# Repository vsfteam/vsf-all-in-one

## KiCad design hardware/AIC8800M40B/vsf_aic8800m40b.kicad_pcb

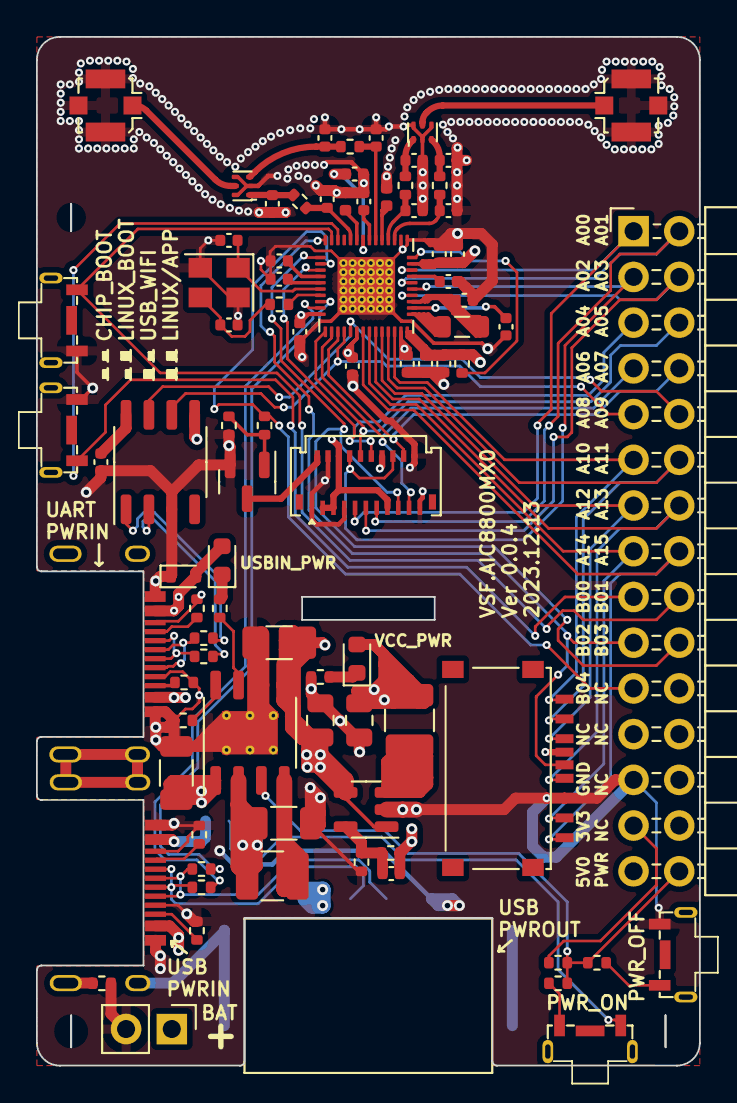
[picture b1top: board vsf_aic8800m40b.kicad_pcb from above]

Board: 4 copper layers, 36.8 x 57.2 mm, 86 parts (1 on the bottom side), 78 nets.

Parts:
BT1: Battery; PinHeader_1x02_P2.54mm_Vertical
C1, C2, C3, C4, C5, C7, C8, C10, C11, C13, C14: 1uF; C_0402_1005Metric
C6, C9, C12: 4.7uF; C_0402_1005Metric
C15, C17, C19, C21, C29: NC; C_0402_1005Metric
C16: 1pF; C_0402_1005Metric
C18, C20: 0.5pF; C_0402_1005Metric
C22: 1.5nH; C_0402_1005Metric
C23: 0.1uF; C_0402_1005Metric
C24, C25: 10uF; C_1206_3216Metric
C26: 22uF; C_1206_3216Metric
C27, C28: 10uF; C_0805_2012Metric
C30: 0Ohm; C_0402_1005Metric
C31: 22pF; C_0402_1005Metric
D1: LESD5Z5.0CT1G; D_SOD-523
D2: LED, RED; LED_0603_1608Metric
D3: LED,GREEN; LED_0603_1608Metric
J1: USB_A; USB-A-8.5_DOWN3.4
J2, J3: USB_C_Receptacle_USB2.0; USB_C_Receptacle_Palconn_UTC16-G_DOWN1.6
J4: Micro_SD_Card_Det1; MicroSD_Tiny
J5: Molex_502250-2191_2Rows-21Pins-1MP_P0.60mm_Horizontal
J6, J7: Conn_Coaxial; U.FL_Molex_MCRF_73412-0110_Vertical
J8: Conn_02x15_Odd_Even; PinHeader_2x15_P2.54mm_Horizontal
JP1: Jumper_3_Open; SolderJumper-3_P1.3mm_Open_RoundedPad1.0x1.5mm_NumberLabels
L1: 4.7uH, 0805, Isat>=250mA, Rdc<=300mOhm; L_0805_2012Metric
L2: 1.2nH; L_0402_1005Metric
L3: 1.4nH; L_0402_1005Metric
L4: 2.2uH 1.2A; L_1210_3225Metric
L5: 4.7uH; L_1210_3225Metric
Q1: S9013; SOT-23
R1: 1.5nH; R_0402_1005Metric
R2: 1.2pF; R_0402_1005Metric
R3: 2pF; R_0402_1005Metric
R4: 3pF; R_0402_1005Metric
R5: 0; R_0402_1005Metric
R6, R7, R10, R11: 5.1k; R_0402_1005Metric
R8, R9, R12, R13: 22; R_0402_1005Metric
R14: 2k, 1%; R_0402_1005Metric
R15: 10k; R_0402_1005Metric
R16: 3.3k; R_0402_1005Metric
R17, R21: 1k; R_0402_1005Metric
R18: 22K,1%; R_0402_1005Metric
R19: 100K,1%; R_0402_1005Metric
R20, R22, R24: 47k; R_0402_1005Metric
R23: NC; R_0402_1005Metric
R25: 4.7k; R_0402_1005Metric
SW1, SW2, SW3, SW4: SW_Push; JHA004
U1: AIC8800MX0_48P; QFN-48.10.14.10.14-1EP_5x5mm_P0.35mm_EP3.7x3.7mm_ThermalVias
U2: CH340N; SOP-8_3.9x4.9mm_P1.27mm
U3: ETA9638; HSOP-8-1EP_3.9x4.9mm_P1.27mm_EP2.41x3.1mm_ThermalVias
U4: ETA3486; SOT-23-5
U5, U6: Filter_SLFD18-5R950G-07T
Y1: 40M, 10PPM,10pF; Oscillator_SMD_Abracon_ASE-4Pin_3.2x2.5mm

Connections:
/GPIOA0: J5.9 (SCL), J8.1, U1.32 (GPIOA0)
/GPIOA1: J5.13 (CS), J8.2, U1.30 (GPIOA1)
/GPIOA2: J5.8 (RESET), J5.16 (TP_RESET), J8.3, U1.29 (GPIOA2)
/GPIOA3: J5.11 (SDA), J8.4, U1.28 (GPIOA3)
/GPIOA4: J5.12 (RS), J8.5, U1.3 (GPIOA4)
/GPIOA5: J5.10 (TE), J8.6, U1.11 (GPIOA5)
/GPIOA6: J5.19 (TP_SCL), J8.7, U1.12 (GPIOA6)
/GPIOA7: J5.18 (TP_SDA), J8.8, U1.13 (GPIOA7)
/GPIOA8: J8.9, U1.14 (GPIOA8), U2.6 (TXD)
/GPIOA9: J8.10, U1.15 (GPIOA9), U2.7 (RXD)
/GPIOA10: J4.1 (DAT2), J8.11, U1.22 (GPIOA10)
/GPIOA11: J4.2 (DAT3/CD), J8.12, U1.21 (GPIOA11)
/GPIOA12: J4.3 (CMD), J8.13, U1.20 (GPIOA12)
/GPIOA13: J4.5 (CLK), J8.14, U1.19 (GPIOA13)
/GPIOA14: J4.7 (DAT0), J8.15, U1.18 (GPIOA14)
/GPIOA15: J4.8 (DAT1), J8.16, U1.17 (GPIOA15)
/GPIOB0: J8.17, SW3.1, U1.46 (GPIOB0)
/GPIOB1: J8.18, SW4.2, U1.47 (GPIOB1)
/GPIOB2: J4.9 (DET), J8.19, U1.48 (GPIOB2)
/GPIOB3: J5.17 (TP_INT), J8.20, U1.1 (GPIOB3)
/GPIOB4: J8.21, R17.1, U1.2 (GPIOB4)
/PWREN: J8.30, R20.1, R21.1, R22.2, U3.3 (EN)
/PWRKEY: R24.1, U1.34 (PWR_WF)
/PWR_3V3: C4.1, C6.1, C7.1, C11.1, C12.1, C28.1, C31.2, D3.2 (A), J4.4 (VDD), J5.3 (LEDA), J5.5 (VCC), J5.6 (VCC), J5.15 (TP_VDD), J8.27, L5.2, R19.2, R22.1, R24.2, U1.16 (VIO), U1.24 (VBAT), U1.33 (VDD33_PA)
/Shield: J1.5 (Shield), J2.S1 (SHIELD), J3.S1 (SHIELD), R5.2
/USB5V_IN: C25.1, D1.2 (A2), D2.2 (A), J2.A4 (VBUS), J2.A9 (VBUS), J2.B4 (VBUS), J2.B9 (VBUS), J3.A4 (VBUS), J3.A9 (VBUS), J3.B4 (VBUS), J3.B9 (VBUS), JP1.3 (B), U2.5 (VCC), U3.1 (VIN)
/USB5V_OUT: C26.1, C27.1, J1.1 (VBUS), J8.29, U3.5 (OUT), U4.1 (EN), U4.4 (IN)
/USBUart_DM: R12.1, U2.2 (UD-)
/USBUart_DP: R13.1, U2.1 (UD+)
/USB_DM: R8.1, U1.9 (USB_DM)
/USB_DP: R9.1, U1.8 (USB_DP)
/VBAT: BT1.1 (+), C24.1, JP1.1 (A), L4.1, U3.2 (BAT)
/V_CORE: C3.1, C5.1, U1.10 (V_CORE), U1.23 (V_CORE)
/_USB_DM: J1.2 (D-), J2.A7 (D-), J2.B7 (D-), R8.2
/_USB_DP: J1.3 (D+), J2.A6 (D+), J2.B6 (D+), R9.2
GND: BT1.2 (-), C1.2, C2.2, C3.2, C4.2, C5.2, C6.2, C7.2, C8.2, C9.1, C10.2, C11.2, C12.2, C13.1, C14.1, C15.2, C16.2, C17.1, C18.1, C19.2, C20.2, C21.1, C22.1, C23.2, C24.2, C25.2, C26.2, C27.2, C28.2, C29.1, C30.1, D1.1 (A1), J1.4 (GND), J2.A1 (GND), J2.A8 (SBU1), J2.A12 (GND), J2.B1 (GND), J2.B8 (SBU2), J2.B12 (GND), J3.A1 (GND), J3.A8 (SBU1), J3.A12 (GND), J3.B1 (GND), J3.B8 (SBU2), J3.B12 (GND), J4.6 (VSS), J5.1 (GND), J5.4 (GND), J5.7 (GND), J5.14 (GND), J5.20 (GND), J5.21 (GND), J6.2 (Ext), J7.2 (Ext), J8.25, L2.2, L3.2, Q1.2 (E), R5.1, R6.1, R7.1, R10.1, R11.1, R14.1, R16.2, R18.1, R25.1, SW2.1, SW3.2, SW4.1, U1.35 (AVSS), U1.36 (AVSS), U1.49 (PGND), U2.3 (GND), U3.6 (GND), U3.9 (PGND), U4.2 (GND), U5.2 (GND), U5.4 (GND), U5.6 (GND), U6.2 (GND), U6.4 (GND), U6.6 (GND), Y1.2, Y1.4
unnamed: C1.1, U1.4 (AVDD)
unnamed: C10.1, U1.31 (AVDD)
unnamed: C14.2, U1.41 (AVDD)
unnamed: C30.2, R23.2, Y1.3
unnamed: D2.1 (K), R15.1
unnamed: D3.1 (K), R25.2
unnamed: J2.A5 (CC1), R6.2
unnamed: J2.B5 (CC2), R7.2
unnamed: J3.A5 (CC1), R10.2
unnamed: J3.B5 (CC2), R11.2
unnamed: J3.A6 (D+), J3.B6 (D+), R13.2
unnamed: J3.A7 (D-), J3.B7 (D-), R12.2
unnamed: J5.2 (LEDK), Q1.3 (C)
unnamed: J6.1 (In), U6.5 (RFIN)
unnamed: J7.1 (In), U5.5 (RFIN)
unnamed: JP1.2 (C), SW1.1
unnamed: Q1.1 (B), R16.1, R17.2
unnamed: R20.2, SW1.2
unnamed: R21.2, SW2.2
unnamed: C2.1, U1.5 (AVDD18)
unnamed: L2.1, U1.43 (BT_IND)
unnamed: C15.1, R1.1, U1.44 (BT_RF)
unnamed: C13.2, U1.42 (DVDD_BT)
unnamed: R23.1, U1.7 (GPIOB5/GPIOA4/XTAL1)
unnamed: L1.1, U1.25 (SW)
unnamed: C8.1, U1.26 (V_FLS)
unnamed: C9.2, L1.2, U1.27 (V_RF)
unnamed: C17.2, R2.1, U1.40 (WF_AUX5G)
unnamed: L3.1, U1.39 (WF_IND2G4)
unnamed: C21.2, R4.2, U1.38 (WF_RF2G4)
unnamed: C19.1, R3.2, U1.37 (WF_RF5G)
unnamed: C29.2, U1.6 (XTAL0/XTAL2), Y1.1
unnamed: C23.1, U2.8 (V3)
unnamed: R14.2, U3.8 (ISET)
unnamed: R15.2, U3.7 (LED)
unnamed: L4.2, U3.4 (SW)
unnamed: C31.1, R18.2, R19.1, U4.5 (FB)
unnamed: L5.1, U4.3 (SW)
unnamed: C16.1, R1.2, U5.1 (TR_2)
unnamed: C18.2, R2.2, U5.3 (TR_5)
unnamed: C22.2, R4.1, U6.1 (TR_2)
unnamed: C20.1, R3.1, U6.3 (TR_5)

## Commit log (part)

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2025-11-23 deinit all submodule for 67c6748b37653a475737b31aa94090dd377e18a4
2025-11-23 deinit all submodule for 241f0f3141b1af206fd4cd717d137e0215628786
2025-11-23 deinit all submodule for 46751e3c4d48f65713b1ebfaccb9fc89bf2c1604
2025-11-24 deinit all submodule for f488ea8ebc493cd1f46af47aad82aea8ea483b33
2025-11-24 deinit all submodule for 0d4e00daae5dd0818de6482a9c8eb6f83fbaa81c
2025-11-25 deinit all submodule for 84ca6d32016b4e58052714eba8875ccaa916a2fd
2025-11-26 deinit all submodule for 1fe6967d62fdfcb8645fece445edbb5880c0e5e0
2025-11-27 deinit all submodule for c454ac5021eec62cac1831503f70fdc47d3390b8
2025-11-27 deinit all submodule for 8302c955d58b9c3bc166fd5dcaa231e36d9bcef3
2025-11-30 deinit all submodule for c9cc5a41fb4785dbfd62c2cab5b4bd28d9d0b040
2025-11-30 deinit all submodule for 60ad4ff32f29e7884f1b45e49e0b9bb7584a3cf2
2025-12-01 deinit all submodule for 2a0cdc3849d2dd170f168dff3a44f6407067da6f
2025-12-02 deinit all submodule for 13bcafacbf2a68f7ad58c9b405cec5100c1fb602
2025-12-03 deinit all submodule for 91f710a716426a763c1996f13a4717ee8e5290d5
2025-12-06 deinit all submodule for 54996d013b9e020c9196c0f5f0f1da3eb48f448a
2025-12-06 deinit all submodule for 7ca5c2a82b42c218baeacfef081bf111986a2cfb
2025-12-06 deinit all submodule for 70b20738e6a00e9c116abbae0a82220c2b54c5d5
2025-12-07 deinit all submodule for 8f11dbbc2d7e0d3e612490da0b40e4152df5825f
2025-12-07 deinit all submodule for 1a4df24a76aa64f36859f1a7ae4bd612f4f1f845
2025-12-08 deinit all submodule for ada699f35ef9eceaef6f5d354710a9d4546c1f7a
2025-12-09 deinit all submodule for 1a5e6422de9264f9e671bfa76eefbaa415ed6c63
2025-12-09 deinit all submodule for b15210f9d8d4f262e55cbbb0479cfc2c6b4b805a
2025-12-09 deinit all submodule for 2edd0f1f26176a1000c9a3a329e4eb4edb7b8663
2025-12-09 deinit all submodule for f33b89fd32b5cfafa6c9ebab11a6d4132b9091a2
2025-12-10 deinit all submodule for ee8e61d9b985f4b51fb24e0c51809001ceb12445
2025-12-13 deinit all submodule for 27a1f1232ef3e530a8754a8ed54ad5afb66dfb92
2025-12-14 deinit all submodule for 0d68f41451c570eee8c5b08a1f6801e8aee343b1
2025-12-14 deinit all submodule for fbf600ea5e5329e52b279723d22f5d1fd6545c2c
2025-12-15 deinit all submodule for 377eb249e63b8b4f633d458723ffcf0ab4daa780
2025-12-15 deinit all submodule for b200d1a1837474690b9582fb817cf284c7b8fe1d
2025-12-16 deinit all submodule for 0a82d5855b047f604f160341d685d76d436c8901
2025-12-16 deinit all submodule for ea6d5840ae73c880af906d095dd43fd93f298e12
2025-12-16 deinit all submodule for 6c02c676f9b04d4dd670c8b550b638032c644ad1
2025-12-19 deinit all submodule for 5ba5714c1b66f71c11868e9209bebb2f890e5be8
2025-12-20 deinit all submodule for 8588c837ba9719414a46b731ee40c6ba9c7db12c
2025-12-21 deinit all submodule for d90f558b59ce35b46576cfdfda6fa407c457cd1a
2025-12-22 deinit all submodule for f8db8e8f7d4df939fa51891abc0af786b0fc5ba8
2025-12-22 deinit all submodule for fe698cf9b8eb3e870e96a6ad059fac144976dc7c
2025-12-25 deinit all submodule for fc6ec1ec2cf697438c5d211e5dbc067827d54f85
2025-12-25 deinit all submodule for 8faeb060e008ec6d12f925cb591dd4cb22258fac
2025-12-29 deinit all submodule for 68f9e3747096dbbdd3d822ec8809272a8ce496b0
2025-12-31 deinit all submodule for cc781a27a2f867eb89e9d3a3ff8ec9f006526c53
2025-12-31 deinit all submodule for af87c609369fae4bfbadef55653c538320e7ac73
2026-01-05 deinit all submodule for 2e55a9cefbe0c8d6b654892c1b69c4b3d9230cdc
2026-01-05 deinit all submodule for f914394c590ae7993ac55b6251424fcc683857df
2026-01-07 deinit all submodule for dc300b967a80da60b79dfa14def94700a6b0abd1
2026-01-09 deinit all submodule for 3a2f1ef1532e96878f3cb1faf3693e1bcb39ad13
2026-01-09 deinit all submodule for 9388752da8e9eacab8727289eada077fa812cd24
2026-01-11 deinit all submodule for 45cae1dda9abee9ddcafe0428cf54565aa938218
2026-01-12 deinit all submodule for 363573d94b23cbecc721397566c1d2853a14a2a4
2026-01-14 deinit all submodule for 33dc4e4bc71989749c9ee75ca3fb18f1b2055b66
2026-01-16 deinit all submodule for 9e924c1637f267b8aced93f1a3a427ba0c60a68d
2026-01-16 deinit all submodule for 33e4fd52e0a915434abc141c5c1d1c14f6a28b0d
2026-01-16 deinit all submodule for 64a803e83c4505ce5749832d1aedd3175feaf4ac
2026-01-16 deinit all submodule for f791cd45b61363379a65582a57107ec3aa8db840
2026-01-17 deinit all submodule for 541687a3e3fe7dc15cedeb654b148cd38ae7a468
2026-01-17 deinit all submodule for 412f1513b7c77f561f86782feaed5e737a920817
2026-01-17 deinit all submodule for 3a9f7e7ac8f68d56fe5e0983c8b663bcca22acc9
2026-01-17 deinit all submodule for b12419842c874f052a05b6b706846ce4676f2b2f
2026-01-17 deinit all submodule for 521e99c0600826ec69cda30b74059d21edcf015a
2026-01-18 deinit all submodule for 717a1105d3d3cf54a16e5d6a76ba22c6f53b7a79
2026-01-18 deinit all submodule for c4946e3e2bf8c186dc50c2015bef68bc383520de
2026-01-18 deinit all submodule for da1b648790704558c2d8378a62d9ed4929cfc0d4
2026-01-18 deinit all submodule for 55bf622d2b5881b2ed0f1b5c4398b7c737ffabb5
2026-01-19 deinit all submodule for b2e9e8ac451ce3e22daa3f9fb74a147f4fb0bf21
2026-01-19 deinit all submodule for 6d6064e8ca00db6157427bc006f55d0de10602ff
2026-01-20 deinit all submodule for d74fc2372d645381ec6dc2f891d43d910871d73f
2026-01-20 deinit all submodule for 151431e189d28812fb6d3d960420d0d228c1995f
2026-01-20 deinit all submodule for a1d3c4c7bd4bb385c29278608aae13b3f6831ef4
2026-01-20 deinit all submodule for 39668565265a44271fca313763b1b187af268a03
2026-01-21 deinit all submodule for b7adb13d4867efd690f02a03a0aa4c7f7c34f9c2
2026-01-21 deinit all submodule for b82ceea5c571caeaefd85a5725a42e7af7f092cf
2026-01-22 deinit all submodule for b932de86b4844d1d1d1e2bdc70b6c7fc52713c9f
2026-01-22 deinit all submodule for 798608e111bea1246d095bc39e43e653bef8c7bf
2026-01-23 deinit all submodule for c665119012fb9a5a371413f974a5b01d358ba29e
2026-01-23 deinit all submodule for 15b657888ffbcb109cc56cd85ce499cc2cd9ea50
2026-01-23 deinit all submodule for b544508c772df45355815274ff8bfb75202f425d
2026-01-24 deinit all submodule for 7778ae5880d637de3434a8da282daf4521b1e77a
2026-01-24 deinit all submodule for b21c5831af459cb85f2f4fd89424b01148ec901e
2026-01-24 deinit all submodule for 256e43791427e20dcfe2a46c12d6e479f3067f08
2026-01-24 deinit all submodule for f173c1d2d842f878476fd3876455cc99b5fdf423
2026-01-26 deinit all submodule for e5ec1af2f5883dfcca494febacff3af3f0523329
2026-01-26 deinit all submodule for 63bd21835c98809117f0c02016af5ec81b4fb04e
2026-02-03 deinit all submodule for 16cad4db5ba4620ca6713d696a606b0a1127d190
2026-02-03 deinit all submodule for cd15067fb703a494bc939c1418c98fef0d07578f
2026-02-05 deinit all submodule for c527146a311d883674f01af854fc556fdcd4dc06
2026-02-05 deinit all submodule for ecaa3038296b3a2f409419d9ddfdafb5db830be3
2026-02-08 deinit all submodule for 8e744cd19fa9be0a0cb9b254f37f8b4eb159fcfd
2026-02-08 deinit all submodule for e1e5fbf80ac2de7262bd284a34171c2e1d99b1aa
2026-02-09 deinit all submodule for 40e860ce9dcd46bf4ba082fc6794016b9204846c
2026-03-06 deinit all submodule for 335a064801eba802862cae725866600e4edfb46e
2026-03-06 deinit all submodule for 377865b8cf1b974a3d7101c3917ce4058748be27
2026-03-21 deinit all submodule for 00219cef72252031c3b47472e17dd548079d9f0c
2026-03-21 deinit all submodule for 1bfd8a7e351e64872544ed50d0262e934a268d51
2026-03-26 deinit all submodule for e3a5574282b0ad47431895512edbc6c3bb79be10
2026-03-28 deinit all submodule for b3f4d635e42057fbfffc9ece4011c1a4987a1cdd
2026-04-09 deinit all submodule for a452ea9a9cf4885089023541e17471d32479ad26
2026-04-09 deinit all submodule for 64707b13b3298dbe0ed59b447352a550667fc0e4
2026-04-14 deinit all submodule for 7be65f9af82cdc5122e73efc76a374cb4584c6e3
2026-04-15 deinit all submodule for 452246d7c2e83a3f966ebf66a27f0715ee017f73
2026-04-16 deinit all submodule for add1c3e3904022b7ddd18dcb0f0f6db6d1a32762
2026-04-16 deinit all submodule for b53c171a5942b099f4ba055800132203522e8adf
2026-04-17 deinit all submodule for b423be612d0e4a90ec15d3c32e668966d815b2b7
2026-04-25 deinit all submodule for a4b3147bdf49fbfa36b494a560376a5e3d69e92f
2026-04-29 [hal/rtc] minor tweak
2026-04-29 deinit all submodule for f607672659790578974464b9bfc957be9230066b
2026-04-30 deinit all submodule for 7f3e4ff8e887925ccd4129cc276e4f6578afbcf6
2026-05-04 deinit all submodule for e0d57f40ca766e9df09bf30a1bf797a78860058d
2026-05-05 deinit all submodule for ed0d9509b1956962dc7c3744d5757679edc4f4df
2026-05-06 deinit all submodule for 7d02355b7f966e60993fa5b44abf5a0dfeaa8704
2026-05-06 deinit all submodule for e8208a76f3bad7078d318cb1d92d7d331473575d
2026-05-06 deinit all submodule for fcf4d99efd08597b7dff2a8851a16f351c483424
2026-05-07 deinit all submodule for e9479fdffeac47bc511e36ef28caa6265c13e5a7
2026-05-07 deinit all submodule for 834d510bf842ae9d81c4fc6d4022f580c9eeceb3
2026-05-07 deinit all submodule for 1cdec6abdd8db504c654d5efd908414e1fbd5750
2026-05-08 deinit all submodule for 1fe26d2b944d1f272e8d79c5eac19ff06caec5bb
2026-05-08 deinit all submodule for 79fbd77d5bc6dcf756e3fe5f59c3b1b35eb2a0e1
2026-05-09 deinit all submodule for c0727476e5741802a7546fed5edea49ce3e5a832
2026-05-09 deinit all submodule for 6688e0da1f6630df1ce13dc8aa96d0d05eac9ed2
2026-05-11 deinit all submodule for 3ab378d7cd569f36d20801aa3699057f1fe0d6a9
2026-05-11 deinit all submodule for 3b63af0911b32f65b7a7bfa8387459d05de076a2
2026-05-11 deinit all submodule for 5c2a601e81cedee32c46405f0204ad6bf96735c4
2026-05-12 deinit all submodule for 0227fdda15f1eb32c35be95d37cf028400f9696d
2026-05-13 deinit all submodule for a418638387731cc7b22493529cd36623910f4292
2026-05-13 deinit all submodule for c3767bf738b926ddf37641da572f7dff2d87f568
2026-06-01 deinit all submodule for 39b2b426929a427f8f08022ff0ecd60937f3dd3e
2026-06-01 deinit all submodule for 66b3c4c2ac71c547ec4233417a2626b767ce69ea
2026-06-03 deinit all submodule for fcd5e42268079aad980208dafc2292c46267deb4
2026-06-03 deinit all submodule for 4d2f0398b47b1c36bf8213b2e02159f68a4e4464
2026-06-04 deinit all submodule for 8fbad0d18b8e0bb482327135f3124da38f3a024f
2026-06-06 deinit all submodule for 58947f5675afccd697c291f81ea077750cd918f6
2026-06-09 deinit all submodule for 7573dc340c3d217f9fc818246a339e18f3e01f5b
2026-06-10 deinit all submodule for be85d85053ae4dd3d26fcd89ac83f194b1ccdd33
2026-06-10 deinit all submodule for 55bf7451ff17f9b3505631d6e07a78e070bb8ea0
2026-06-10 deinit all submodule for e977249167ce8f5087904029dd523c3437e978d7
2026-06-11 deinit all submodule for 08d95352a1b141089b2525e5e380d1577f185ee1
2026-06-11 deinit all submodule for 487d870ea4ab2a08d2e545ba1a74c1bdc381fa7b
2026-06-11 deinit all submodule for d6efeb8b5d17cbc215e16eb2cda9c1ed3d440bbf
2026-06-11 deinit all submodule for 48462b23bb9ad995276cd2ed2099576e3652651f
2026-06-12 deinit all submodule for bc091b85b062de0d15d256ac0dab62b28e3d1dec
2026-06-13 deinit all submodule for c4c250b6ff967810a33c62fb61a555671bcc07ff
2026-06-14 deinit all submodule for bad1bf2c21fe52ee57e6d9499da14872af107c4d
2026-06-14 deinit all submodule for efd3979a69a91c982ceece65c0b2e6cb024010e7
2026-06-14 deinit all submodule for 38c3a6bbe9ebcf24c6487b816a7af393e4de4618
2026-06-14 deinit all submodule for 8b7786083154c9db5d0e8c29172587d388b9405a
2026-06-14 deinit all submodule for 1718aa89eb90da59b447db99852dff0af21b7086
2026-06-14 deinit all submodule for 3ab4d20eca73154ba263c5b02451d0e2ccd57717
2026-06-15 deinit all submodule for e694aab78cbe8f1884d26711f46c8848d6d94159
2026-06-15 deinit all submodule for 135d4d412b85d802e197a028b23ffa4007142fca
2026-06-17 deinit all submodule for 2909000939e8a07c490c2ccb074eb7cf9b4040bf
2026-06-17 deinit all submodule for 1f2844be7a5cc77c5325956d90eb1db2b20e76e4
2026-06-17 deinit all submodule for 81c8834b328b50f30b3363206645cdae3efcb3e7
2026-06-17 deinit all submodule for 4ae0ea9f0d6618a2f65a1e04491cbe082ffef2a2
2026-06-18 deinit all submodule for 606aeaf916e2439b8cfe6dc391a0dfeb3312816f
2026-06-26 deinit all submodule for 09e9d91c425b970b50228b5f34404e425306ecc6
2026-06-27 deinit all submodule for 7dc0fb3c0d1f2374379b81bf5e650369a19014fd
2026-06-27 deinit all submodule for 12749aa4794829f3404157a1f0527852d94fe15c
2026-06-27 deinit all submodule for f87bff9330dd1755f409d958dad6d3507915ad6e
